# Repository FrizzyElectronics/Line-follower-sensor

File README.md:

# Line-follower-sensor
This module uses the TCRT5000 infrared sensor to detect a white/black line. It carries a potentiometer to calibrate it and achieve better results. It's the best companion for creating a line following robot. Remember that you will need two of them to achieve this.

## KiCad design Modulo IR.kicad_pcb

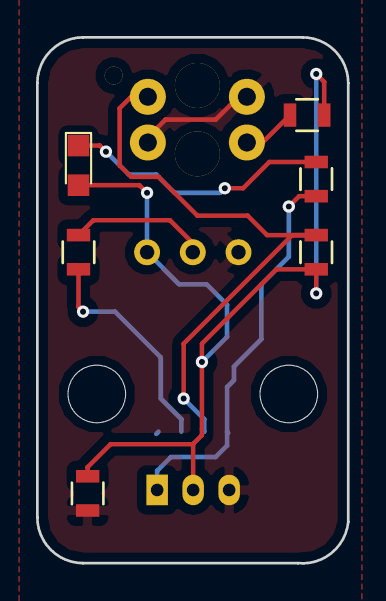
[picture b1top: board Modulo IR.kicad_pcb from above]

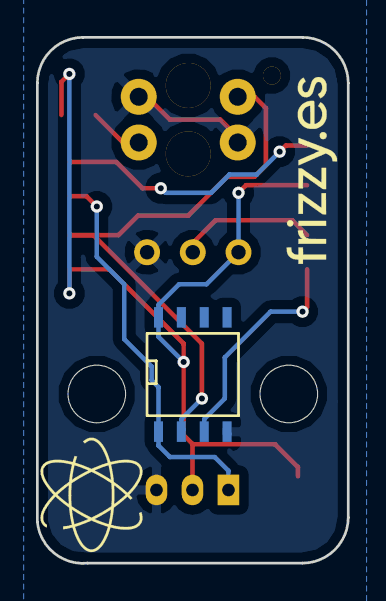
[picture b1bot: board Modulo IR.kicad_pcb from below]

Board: 2 copper layers, 17.3 x 29.2 mm, 10 parts (2 on the bottom side), 8 nets.

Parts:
U1: LM358N; SOIC-8-N
U3: 1K; R_0805
U5: 20K; R_0805
U6: 10K; R_0805
U7: 10k; Potentiometer_Trimmer_Bourns_3296W
U8: CON3_ET; JST_PH_S3B-PH-K_03x2.00mm_Angled
U9: LED; LED_0805
U10: 100nF; R_0805
U12: TCRT5000
U13: 100R; R_0805

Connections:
A0: U1.2, U5.2, U12.4
GNDREF: U1.4, U7.3, U8.3, U10.2, U12.2, U12.3
unnamed: U1.1, U3.2, U8.1
unnamed: U1.3, U6.2
unnamed: U3.1, U9.1
unnamed: U6.1, U7.2
unnamed: U12.1, U13.2
VCC: U1.8, U5.1, U7.1, U8.2, U9.2, U10.1, U13.1

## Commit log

2017-04-24 First iteration
    First iteration of the Hunt sensor module
2017-05-01 Esquema corregido y ERC pasado
2017-05-01 TCRT5000 3D model
    Modelo en 3D del TCRT5000 añadido / TCRT5000 3D model added.
2017-05-01 Modelos 3D añadidos
2017-05-01 Componentes colocados
2017-05-01 Serigrafía
    Diseño en formato reducido y completo del átomo
2017-05-01 Serigrafia realizada y placa mandada a fabrica
2017-06-05 agujeros del potenciometro cambiados a 0.8mm
2018-01-20 Gerbers exportados
    Gerbers exportados para prueba de panelizacion
2018-02-04 potenciometro cambiado
2018-02-05 Logo atom cambiado
2018-02-10 conector cambiado
2018-02-24 Referencia del potenciometro eliminada
2018-03-04 arbol de carpetas cambiado
2018-03-11 Updated module description
2018-05-06 BOM exportado
2018-05-06 gerbers generados
2018-05-07 Nombre pdf cambiado
2018-06-04 Arreglado el error con el footprint del TCRT5000
2018-07-10 Serigrafia del trimmer eliminada
2018-07-14 re-rellenado el plano de masa
2018-07-15 Gerbers exportados
